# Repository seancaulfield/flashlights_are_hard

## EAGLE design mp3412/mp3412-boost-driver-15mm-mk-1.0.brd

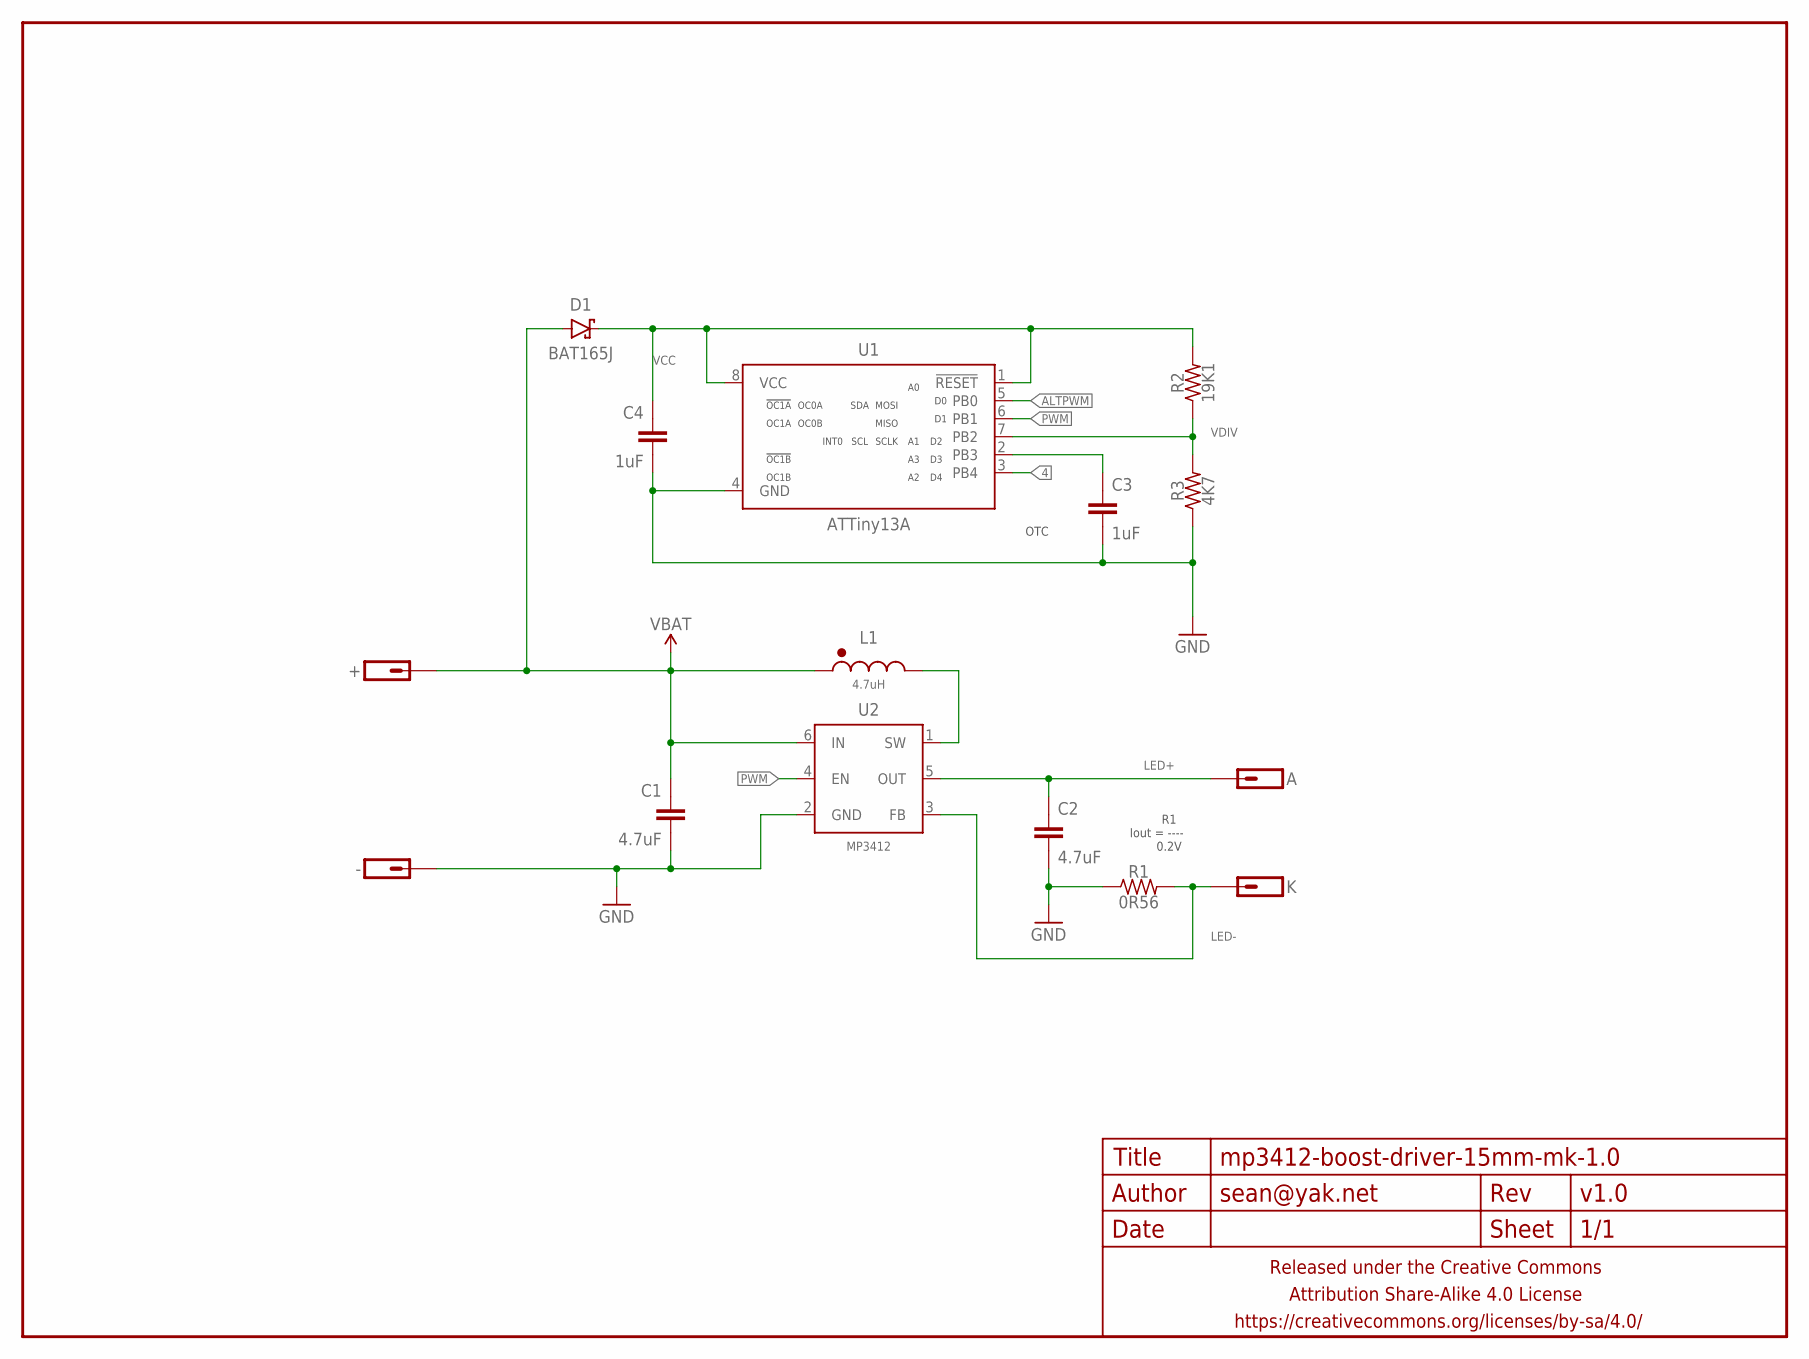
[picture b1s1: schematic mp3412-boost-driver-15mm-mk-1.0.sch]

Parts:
+: M01PTH-1MM-CIR-NS; 1X01-1MM-CIR-NS
-: M01NOT-A-VIA-NOPE; 1X01_NOSILK_NOSTOP
A: M01SMD-1.25MM-DIA; 1X01-SMD-1.25MM-DIA-NS
C1, C2: 4.7uF; C0603-TIGHTER
C3, C4: 1uF; C0402
D1: BAT165J; SOD323-SCHOTTKY
FRAME1: FRAME-LETTERNO_PACKAGE; DUMMY
K: M01SMD-1.25MM-DIA; 1X01-SMD-1.25MM-DIA-NS
L1: 4.7uH; LPS4012-ROUND
R1: 0R56; R0603-TIGHTER
R2: 19K1; R0402
R3: 4K7; R0402
U1: ATTiny13A; SO08-NARROWER
U2: MP3412; TSOT-23-6

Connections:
4: U1.3 (PB4)
ALTPWM: U1.5 (PB0)
GND: -.P$1, C1.2, C2.2, C3.2, C4.2, R1.1, R3.1, U1.4 (GND), U2.2 (GND)
LED+: A.P$1, C2.1, U2.5 (OUT)
LED-: K.P$1, R1.2, U2.3 (FB)
unnamed: C3.1, U1.2 (PB3)
PWM: U1.6 (PB1), U2.4 (EN)
SW: L1.P$2 (2), U2.1 (SW)
VBAT: +.1, C1.1, D1.A, L1.P$1 (1), U2.6 (IN)
VCC: C4.1, D1.C, R2.2, U1.1 (!RESET), U1.8 (VCC)
VDIV: R2.1, R3.2, U1.7 (PB2)

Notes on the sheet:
R1 Iout = ---- 0.2V
OTC

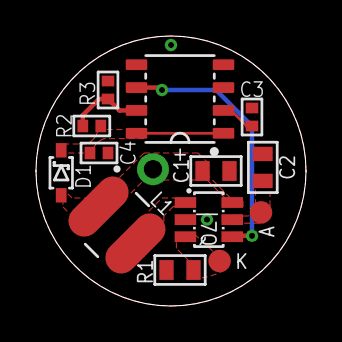
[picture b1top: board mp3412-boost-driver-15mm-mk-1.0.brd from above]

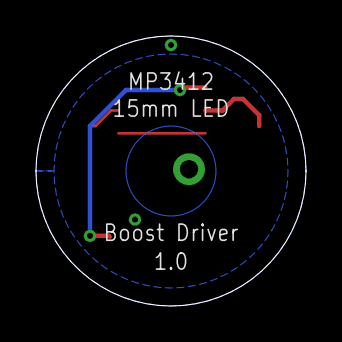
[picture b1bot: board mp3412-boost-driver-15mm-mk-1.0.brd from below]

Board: 2 copper layers, 15.0 x 15.0 mm, 16 parts (2 on the bottom side), 9 nets.

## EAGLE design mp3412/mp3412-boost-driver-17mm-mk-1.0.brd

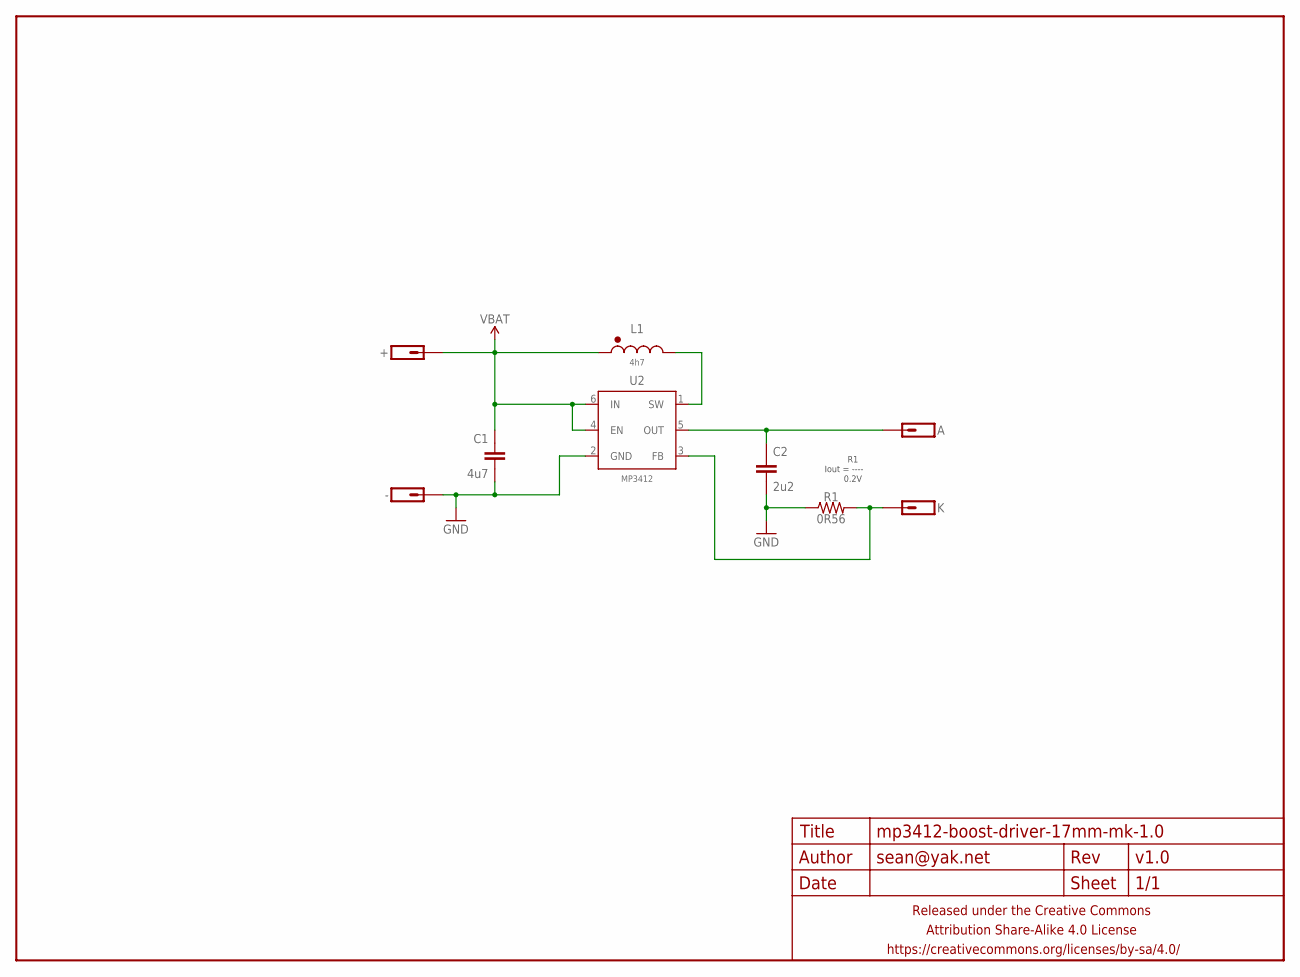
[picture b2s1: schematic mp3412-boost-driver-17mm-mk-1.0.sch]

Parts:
+: M01NOT-A-VIA-NOPE; 1X01_NOSILK_NOSTOP
-: M01NOT-A-VIA-NOPE; 1X01_NOSILK_NOSTOP
A: M01PTH-1MM-CIR-NS; 1X01-1MM-CIR-NS
C1: 4u7; C0603-TIGHTER
C2: 2u2; C0603-TIGHTER
FRAME1: FRAME-LETTERNO_PACKAGE; DUMMY
K: M01PTH-1MM-CIR-NS; 1X01-1MM-CIR-NS
L1: 4h7; EPL2014
R1: 0R56; R0603-TIGHTER
U2: MP3412; TSOT-23-6

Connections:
GND: -.P$1, C1.2, C2.2, R1.1, U2.2 (GND)
unnamed: A.1, C2.1, U2.5 (OUT)
unnamed: K.1, R1.2, U2.3 (FB)
SW: L1.P$2 (2), U2.1 (SW)
VBAT: +.P$1, C1.1, L1.P$1 (1), U2.4 (EN), U2.6 (IN)

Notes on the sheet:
R1 Iout = ---- 0.2V

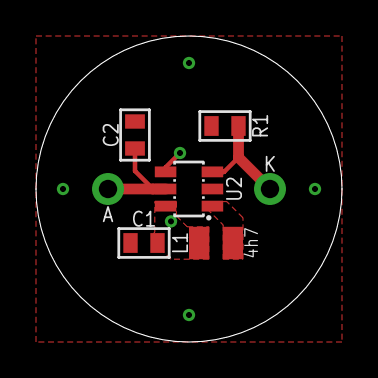
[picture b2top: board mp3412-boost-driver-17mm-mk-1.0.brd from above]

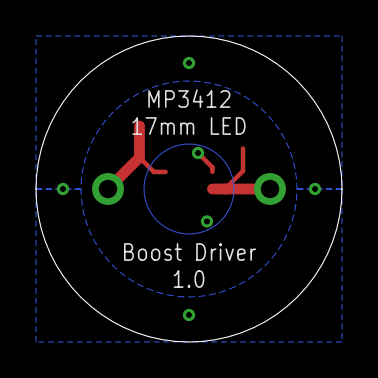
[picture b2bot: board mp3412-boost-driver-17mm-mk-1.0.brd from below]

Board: 2 copper layers, 17.0 x 17.0 mm, 10 parts (2 on the bottom side), 5 nets.

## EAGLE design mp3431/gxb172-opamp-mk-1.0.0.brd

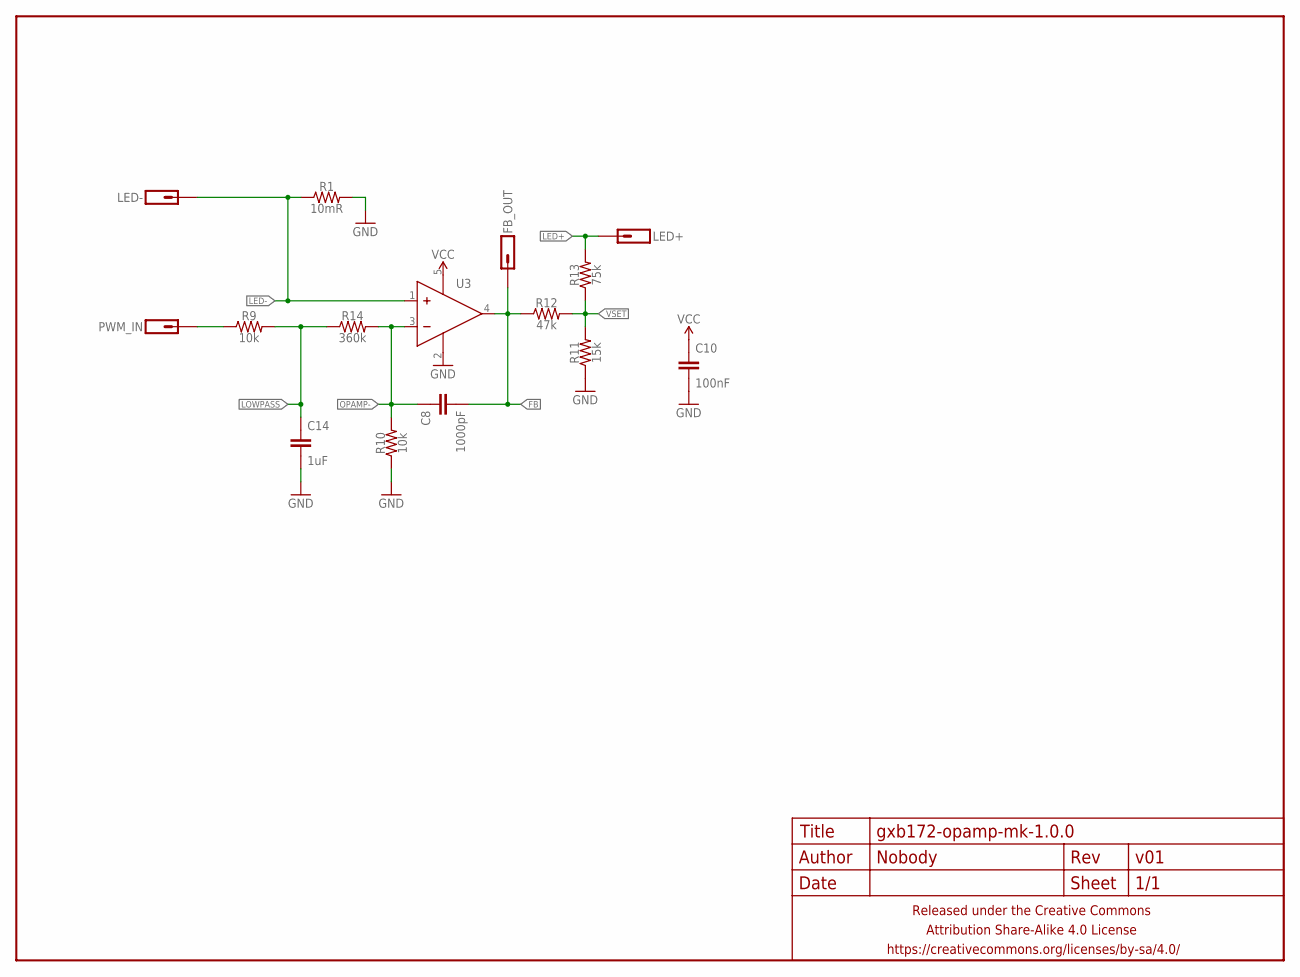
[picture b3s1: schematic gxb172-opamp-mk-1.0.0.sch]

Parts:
C8: 1000pF; C0402
C10: 100nF; C0402
C14: 1uF; C0402
FB_OUT: M01PTH; 1X01
FRAME1: FRAME-LETTERNO_PACKAGE; DUMMY
LED+: M01PTH; 1X01
LED-: M01PTH; 1X01
PWM_IN: M01PTH; 1X01
R1: 10mR; R0805-TIGHTER
R9, R10: 10k; R0402
R11: 15k; R0402
R12: 47k; R0402
R13: 75k; R0402
R14: 360k; R0402
U3: OPAMPOPA333-SC-70; SC70

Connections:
FB: C8.2, FB_OUT.1, R12.1, U3.4 (OUT)
GND: C10.2, C14.2, R1.2, R10.1, R11.1, U3.2 (V-)
LED+: LED+.1, R13.2
LED-: LED-.1, R1.1, U3.1 (IN+)
LOWPASS: C14.1, R9.2, R14.1
OPAMP-: C8.1, R10.2, R14.2, U3.3 (IN-)
PWM_IN: PWM_IN.1, R9.1
VCC: C10.1, U3.5 (V+)
VSET: R11.2, R12.2, R13.1

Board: 2 copper layers, 16 parts (0 on the bottom side), 9 nets, no tracks yet.

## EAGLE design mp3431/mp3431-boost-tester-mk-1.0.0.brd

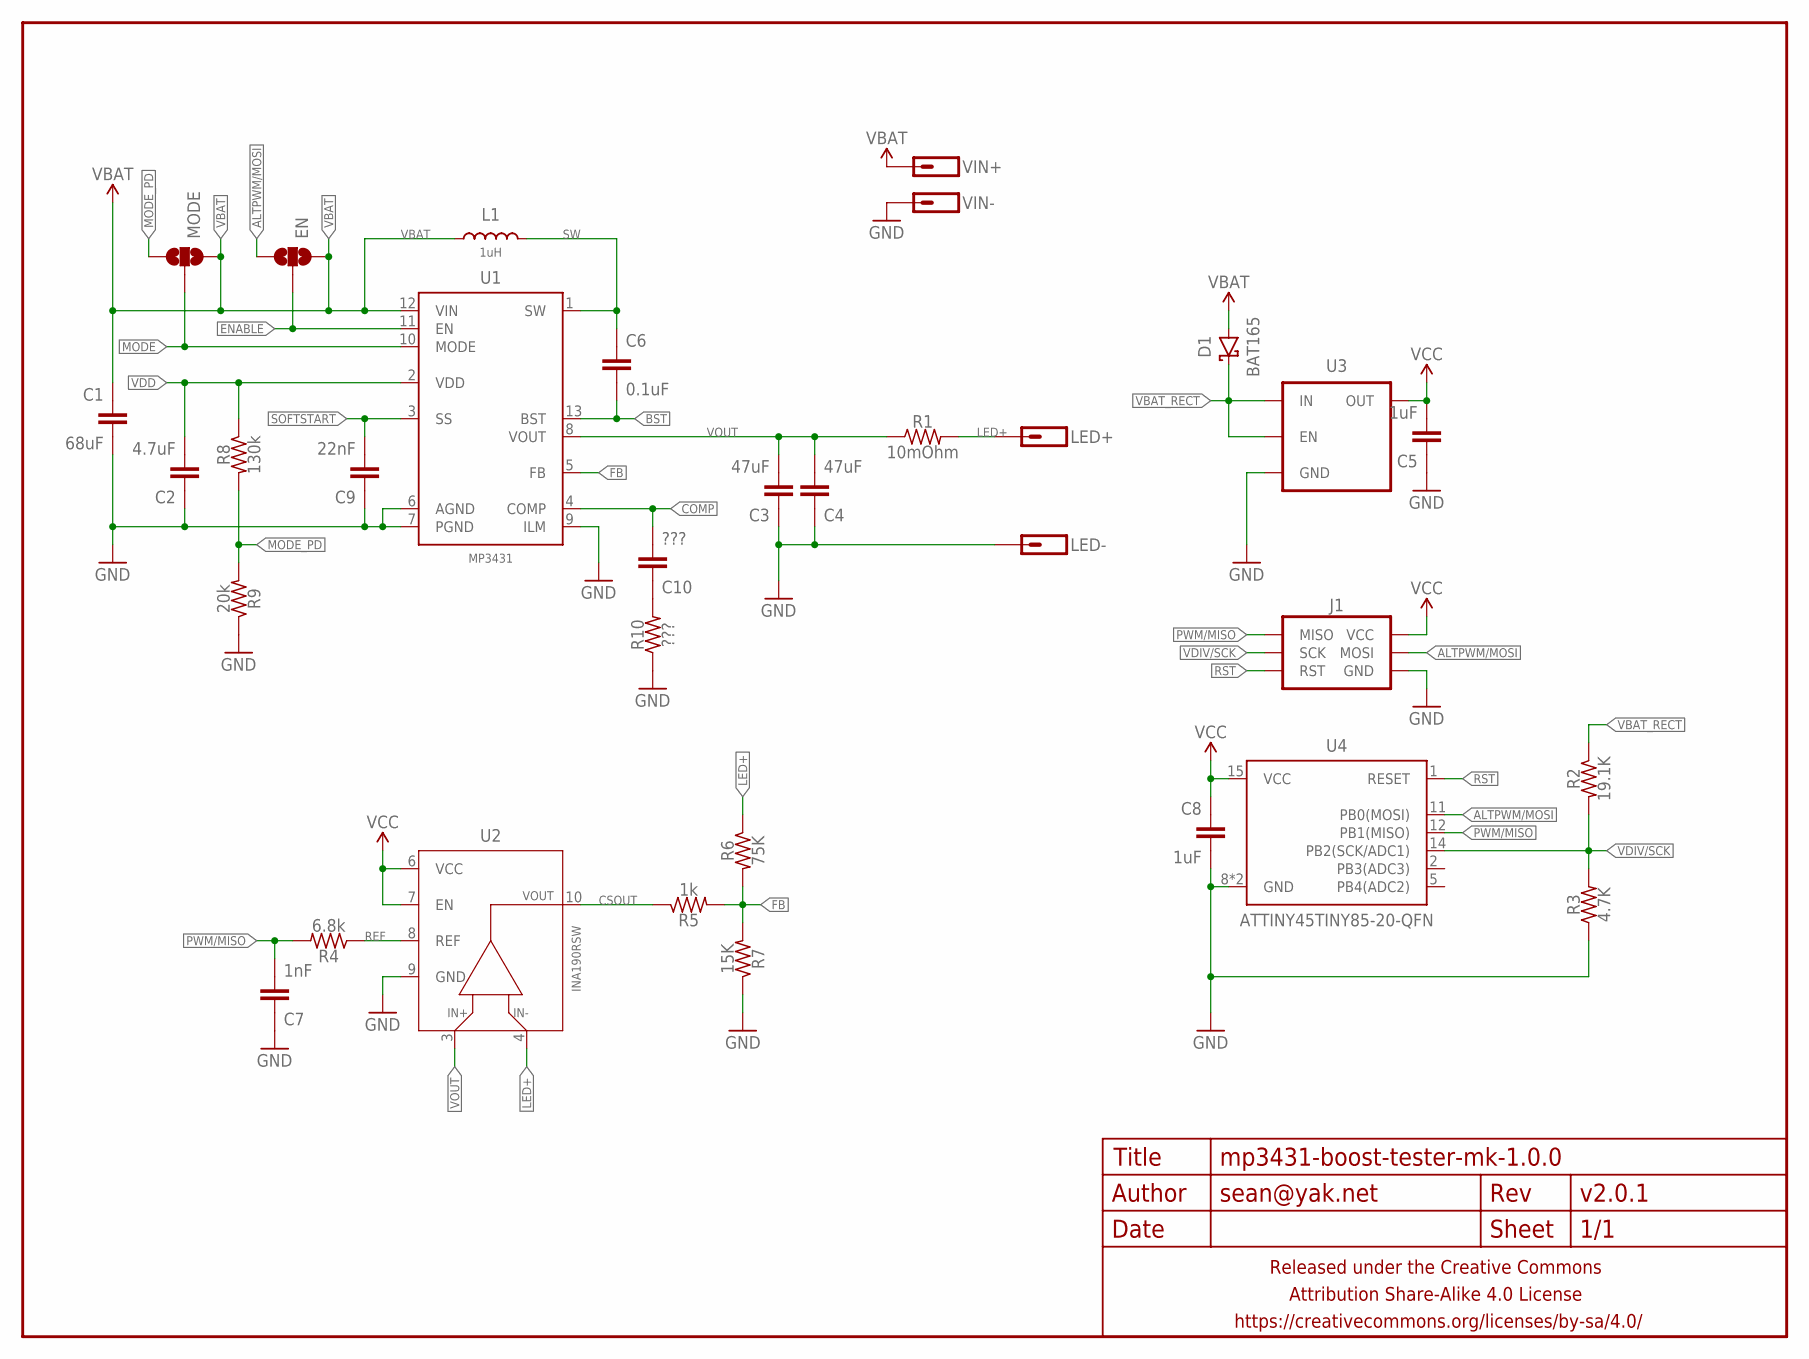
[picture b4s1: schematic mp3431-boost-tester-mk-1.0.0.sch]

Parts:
C1: 68uF; C1206
C2: 4.7uF; C0402
C3, C4: 47uF; C1206
C5, C8: 1uF; C0402
C6: 0.1uF; C0402
C7: 1nF; C0402
C9: 22nF; C0402
C10: ???; C0402
D1: BAT165; SOD323-SCHOTTKY
EN: JUMPER-PAD-3-NOSMALL_BOX_SILK; PAD-JUMPER-3-NO_YES_SILK_SMALL_BOX
FRAME1: FRAME-LETTERNO_PACKAGE; DUMMY
J1: AVR_SPI_PRG_6PTH; 2X3
L1: 1uH; XAL7070
LED+: M01PTH-1.2MM-NS; 1X01-1.2MM-NS
LED-: M01PTH-1.2MM-NS; 1X01-1.2MM-NS
MODE: JUMPER-PAD-3-NOSMALL_BOX_SILK; PAD-JUMPER-3-NO_YES_SILK_SMALL_BOX
R1: 10mOhm; R1206
R2: 19.1K; R0402
R3: 4.7K; R0402
R4: 6.8k; R0402
R5: 1k; R0402
R6: 75K; R0402
R7: 15K; R0402
R8: 130k; R0402
R9: 20k; R0402
R10: ???; R0402
U1: MP3431
U2: INA190RSW; UQFN-10
U3: V_REG_ENTLV700; SC70
U4: ATTINY45TINY85-20-QFN; QFN20
VIN+: M01PTH-1.2MM-NS; 1X01-1.2MM-NS
VIN-: M01PTH-1.2MM-NS; 1X01-1.2MM-NS

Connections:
ALTPWM/MOSI: EN.3, J1.4 (MOSI), U4.11 (PB0(MOSI))
BST: C6.2, U1.13 (BST)
COMP: C10.2, U1.4 (COMP)
COMP_MID: C10.1, R10.2
CSOUT: R5.1, U2.10 (OUT)
ENABLE: EN.2, U1.11 (EN)
FB: R5.2, R6.2, R7.2, U1.5 (FB)
GND: C1.2, C2.1, C3.1, C4.1, C5.1, C7.1, C8.2, C9.1, J1.6 (GND), LED-.P$1, R3.1, R7.1, R9.1, R10.1, U1.6 (AGND), U1.7 (PGND), U1.9 (ILM), U2.9 (GND), U3.2 (GND), U4.8 (GND), U4.PAD (GND), VIN-.P$1
LED+: LED+.P$1, R1.2, R6.1, U2.4 (VIN-)
MODE: MODE.2, U1.10 (MODE)
MODE_PD: MODE.3, R8.2, R9.2
PWM/MISO: C7.2, J1.1 (MISO), R4.2, U4.12 (PB1(MISO))
REF: R4.1, U2.8 (REF)
RST: J1.5 (RST), U4.1 (RESET)
SOFTSTART: C9.2, U1.3 (SS)
SW: C6.1, L1.P$2 (2), U1.1 (SW)
VBAT: C1.1, D1.A, EN.1, L1.P$1 (1), MODE.1, U1.12 (VIN), VIN+.P$1
VBAT_RECT: D1.C, R2.1, U3.1 (IN), U3.3 (EN)
VCC: C5.2, C8.1, J1.2 (VCC), U2.6 (VCC), U2.7 (EN), U3.5 (OUT), U4.15 (VCC)
VDD: C2.2, R8.1, U1.2 (VDD)
VDIV/SCK: J1.3 (SCK), R2.2, R3.2, U4.14 (PB2(SCK/ADC1))
VOUT: C3.2, C4.2, R1.1, U1.8 (VOUT), U2.3 (VIN+)

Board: 2 copper layers, 34 parts (0 on the bottom side), 22 nets, no tracks yet.

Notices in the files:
parts and their libraries:
a_parts: Released under the Creative Commons Attribution Share-Alike 4.0 License
a_parts: https://creativecommons.org/licenses/by-sa/4.0
a_parts: Released under the Creative Commons
